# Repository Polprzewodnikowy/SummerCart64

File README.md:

# SummerCart64 - a fully open source N64 flashcart

**For non-technical description of the SummerCart64, please head to the https://summercart64.dev website!**

## Features

 - **ROM and Save Memory On-board**
   - 64 MiB SDRAM memory for game and save data (enough memory to support every retail game without compromise)
   - 16 MiB FLASH memory for bootloader and extended game data (with extended memory flashcart supports game ROMs up to 78 MiB)

 - **Game Saves**
   - EEPROM 4k/16k, SRAM and FlashRAM save types with an automatic writeback to the SD card (no reset button press required)

 - **Hardware-Dependent Game Features**
   - 64DD add-on emulation
   - Battery backed real time clock (RTC)

 - **Menu**
   - Dedicated open source menu written specifically for this flashcart - [N64FlashcartMenu](https://github.com/Polprzewodnikowy/N64FlashcartMenu)

 - **Game Development**
   - ~23.8 MiB/s peak transfer rate SD card interface
   - ~23.8 MiB/s peak transfer rate USB interface for data upload/download and debug functionality
   - PC app to access the flashcart features:
     - Game/save data upload/download
     - Feature enable control
     - Debug terminal
     - Access to the SD card
     - Firmware update
   - [UNFLoader](https://github.com/buu342/N64-UNFLoader) support
   - IS-Viewer 64 debug interface (fixed 64 kiB buffer with a movable base address)
   - 8 kiB on-chip buffer for general use
   - Status LED and button for general use
   - [UltraCIC_C](https://github.com/jago85/UltraCIC_C) emulation with automatic region switching and programmable seed/checksum values
   - N64 bootloader with support for IPL3 registers spoofing and loading menu from SD card

 - **Cartridge Production**
   - Initial programming via UART header or via dedicated JTAG/SWD interfaces
   - 3D printable shell

---

## Documentation

- [Quick startup guide](./docs/00_quick_startup_guide.md)
- [Memory map](./docs/01_memory_map.md)
- [N64 commands](./docs/02_n64_commands.md)
- [USB interface](./docs/03_usb_interface.md)
- [Config options](./docs/04_config_options.md)
- [FW and SW info](./docs/05_fw_and_sw_info.md)
- [Build guide](./docs/06_build_guide.md)

---

## How do I get one?

Most up to date information about purchasing/manufacturing options is available on https://summercart64.dev website!

If you want to order it yourself then I've prepared all necessary manufacturing files on the [PCBWay Shared Project](https://www.pcbway.com/project/member/shareproject/?bmbno=1046ED64-8AEE-44) site.

**Be careful**: this is an advanced project and it is assumed that you have enough knowledge about electronics.
Selecting wrong options or giving PCB manufacturer wrong information might result in an undesired time and/or money loss.
Boards also come unprogrammed from the manufacturer - you need to do **initial programming step** yourself after receiving the board.
**Price of the components is not included in the initial quote at the checkout** - manufacturer will contact you later with updated price.
To avoid problems _**please**_ read **both** [build guide](./docs/06_build_guide.md) and description on the shared project page **in full**.
If you have even slightest doubt about the ordering or programming process, it is better to leave it to someone experienced - ask in the [N64brew Discord server](https://discord.gg/8VNMKhxqQn) if that's the case.

**Full disclosure**: for every order made through [this link](https://www.pcbway.com/project/member/shareproject/?bmbno=1046ED64-8AEE-44) I will receive 10% of PCB manufacturing and PCB assembly service cost (price of the components is not included in the split). This is a great way of supporting further project development.

If you don't need a physical product but still want to support me then check the sponsor links on the [official website](https://summercart64.dev).

---

## High-level flashcart block diagram

---

## Finished example

---

## Acknowledgement

This project wouldn't be possible without these contributions:

- [64drive](https://64drive.retroactive.be) ([archived](https://web.archive.org/web/20240406215731/https://64drive.retroactive.be/)) orders being on permanent hold long before creating this repository.
- [EverDrive-64 X7](https://krikzz.com/our-products/cartridges/ed64x7.html) being disappointment for homebrew development (slow USB upload, unjustified price and overcomplicated SD card access).
  - Context: Both aforementioned products were priced at $199 in 2020. 64drive features made it a vastly more useful tool for homebrew development.
    Since then, 64drive had never been restocked and EverDrive-64 X7 price was lowered to $159 (as of May 2024).
- [Jan Goldacker (@jago85)](https://github.com/jago85) and his projects:
  - [Brutzelkarte](https://github.com/jago85/Brutzelkarte_FPGA) providing solid base for starting this project and sparking hope for true open source N64 flashcarts.
  - [UltraCIC_C](https://github.com/jago85/UltraCIC_C) reimplementation for easy integration in modern microcontrollers. Thanks also goes to everyone involved in N64 CIC reverse engineering.
- [N64brew](https://discord.gg/WqFgNWf) Discord server community being very helpful during flashcart development.
- [FatFs](http://elm-chan.org/fsw/ff/00index_e.html) FAT32/exFAT library being easiest to integrate in embedded environment.
- [Yakumono's (@LuigiBlood)](https://twitter.com/LuigiBlood) extensive [64DD documentation](https://github.com/LuigiBlood/64dd/wiki) and its implementation in various emulators.
- [Libdragon](https://github.com/DragonMinded/libdragon) open source N64 SDK project and its developers.
- [SERV](https://github.com/olofk/serv) bit-serial 32-bit RISC-V CPU soft core.

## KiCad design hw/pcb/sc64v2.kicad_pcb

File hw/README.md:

# SummerCart64 Hardware

Schematics and PCB design for SummerCart64 done in Autodesk Eagle software.

## TODO

- Expand documentation

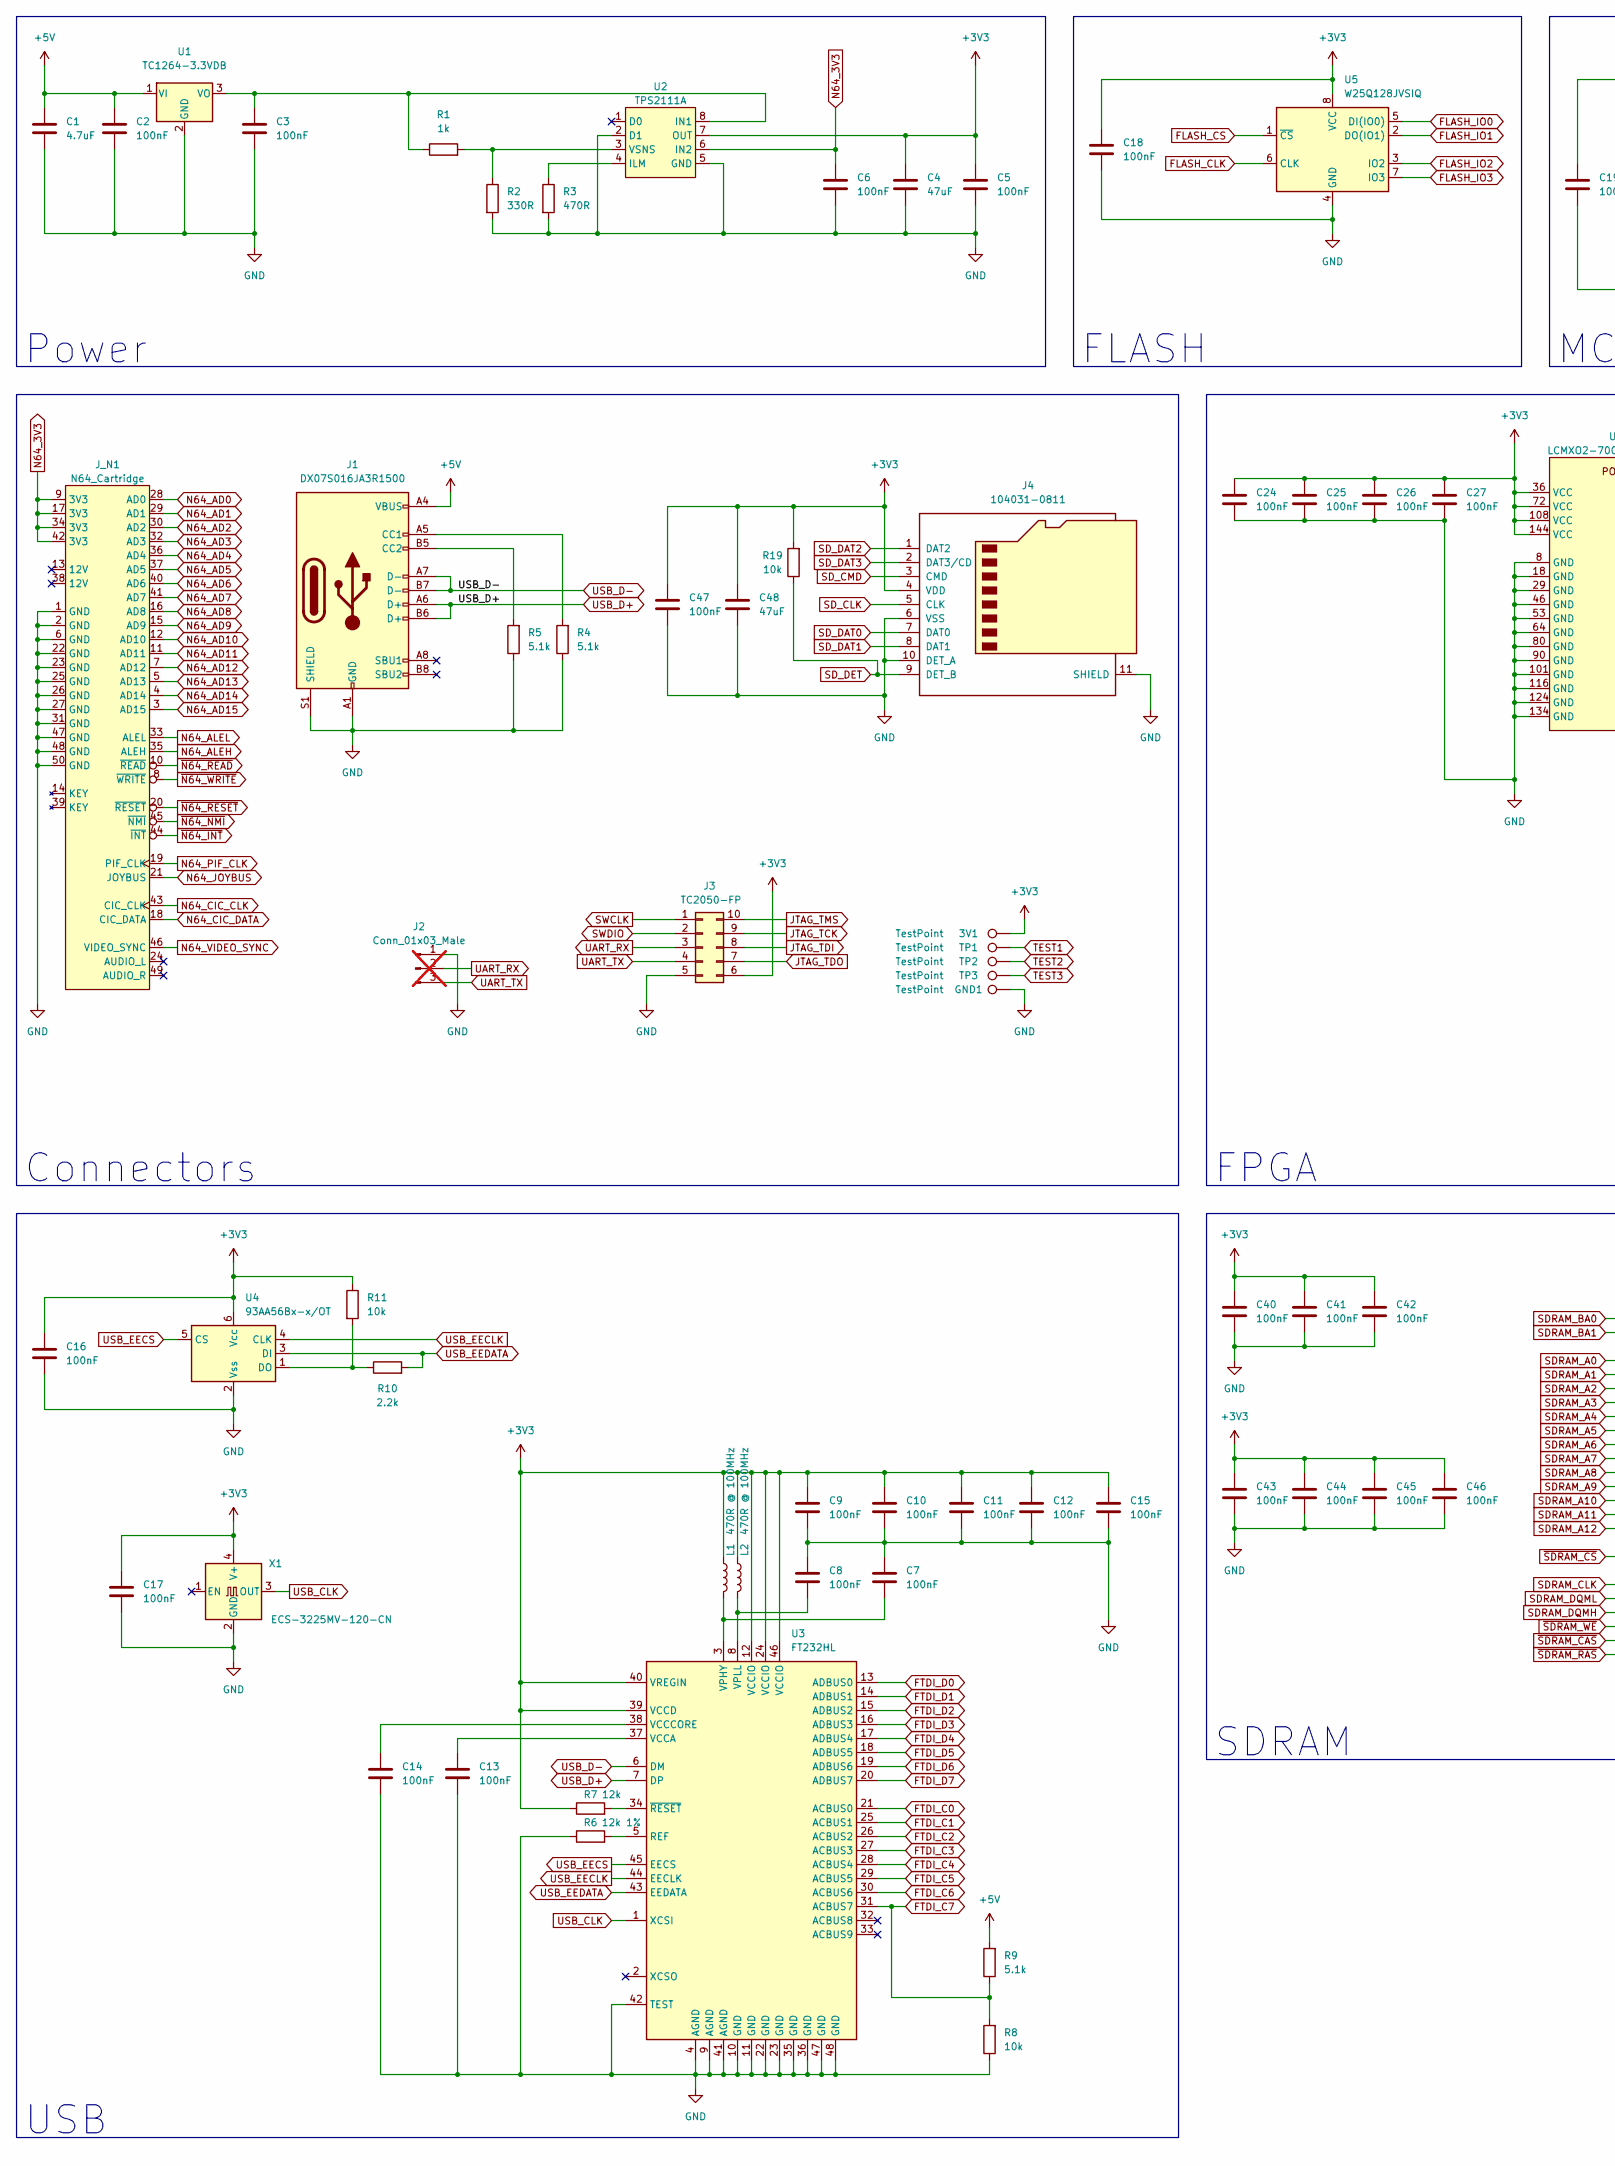
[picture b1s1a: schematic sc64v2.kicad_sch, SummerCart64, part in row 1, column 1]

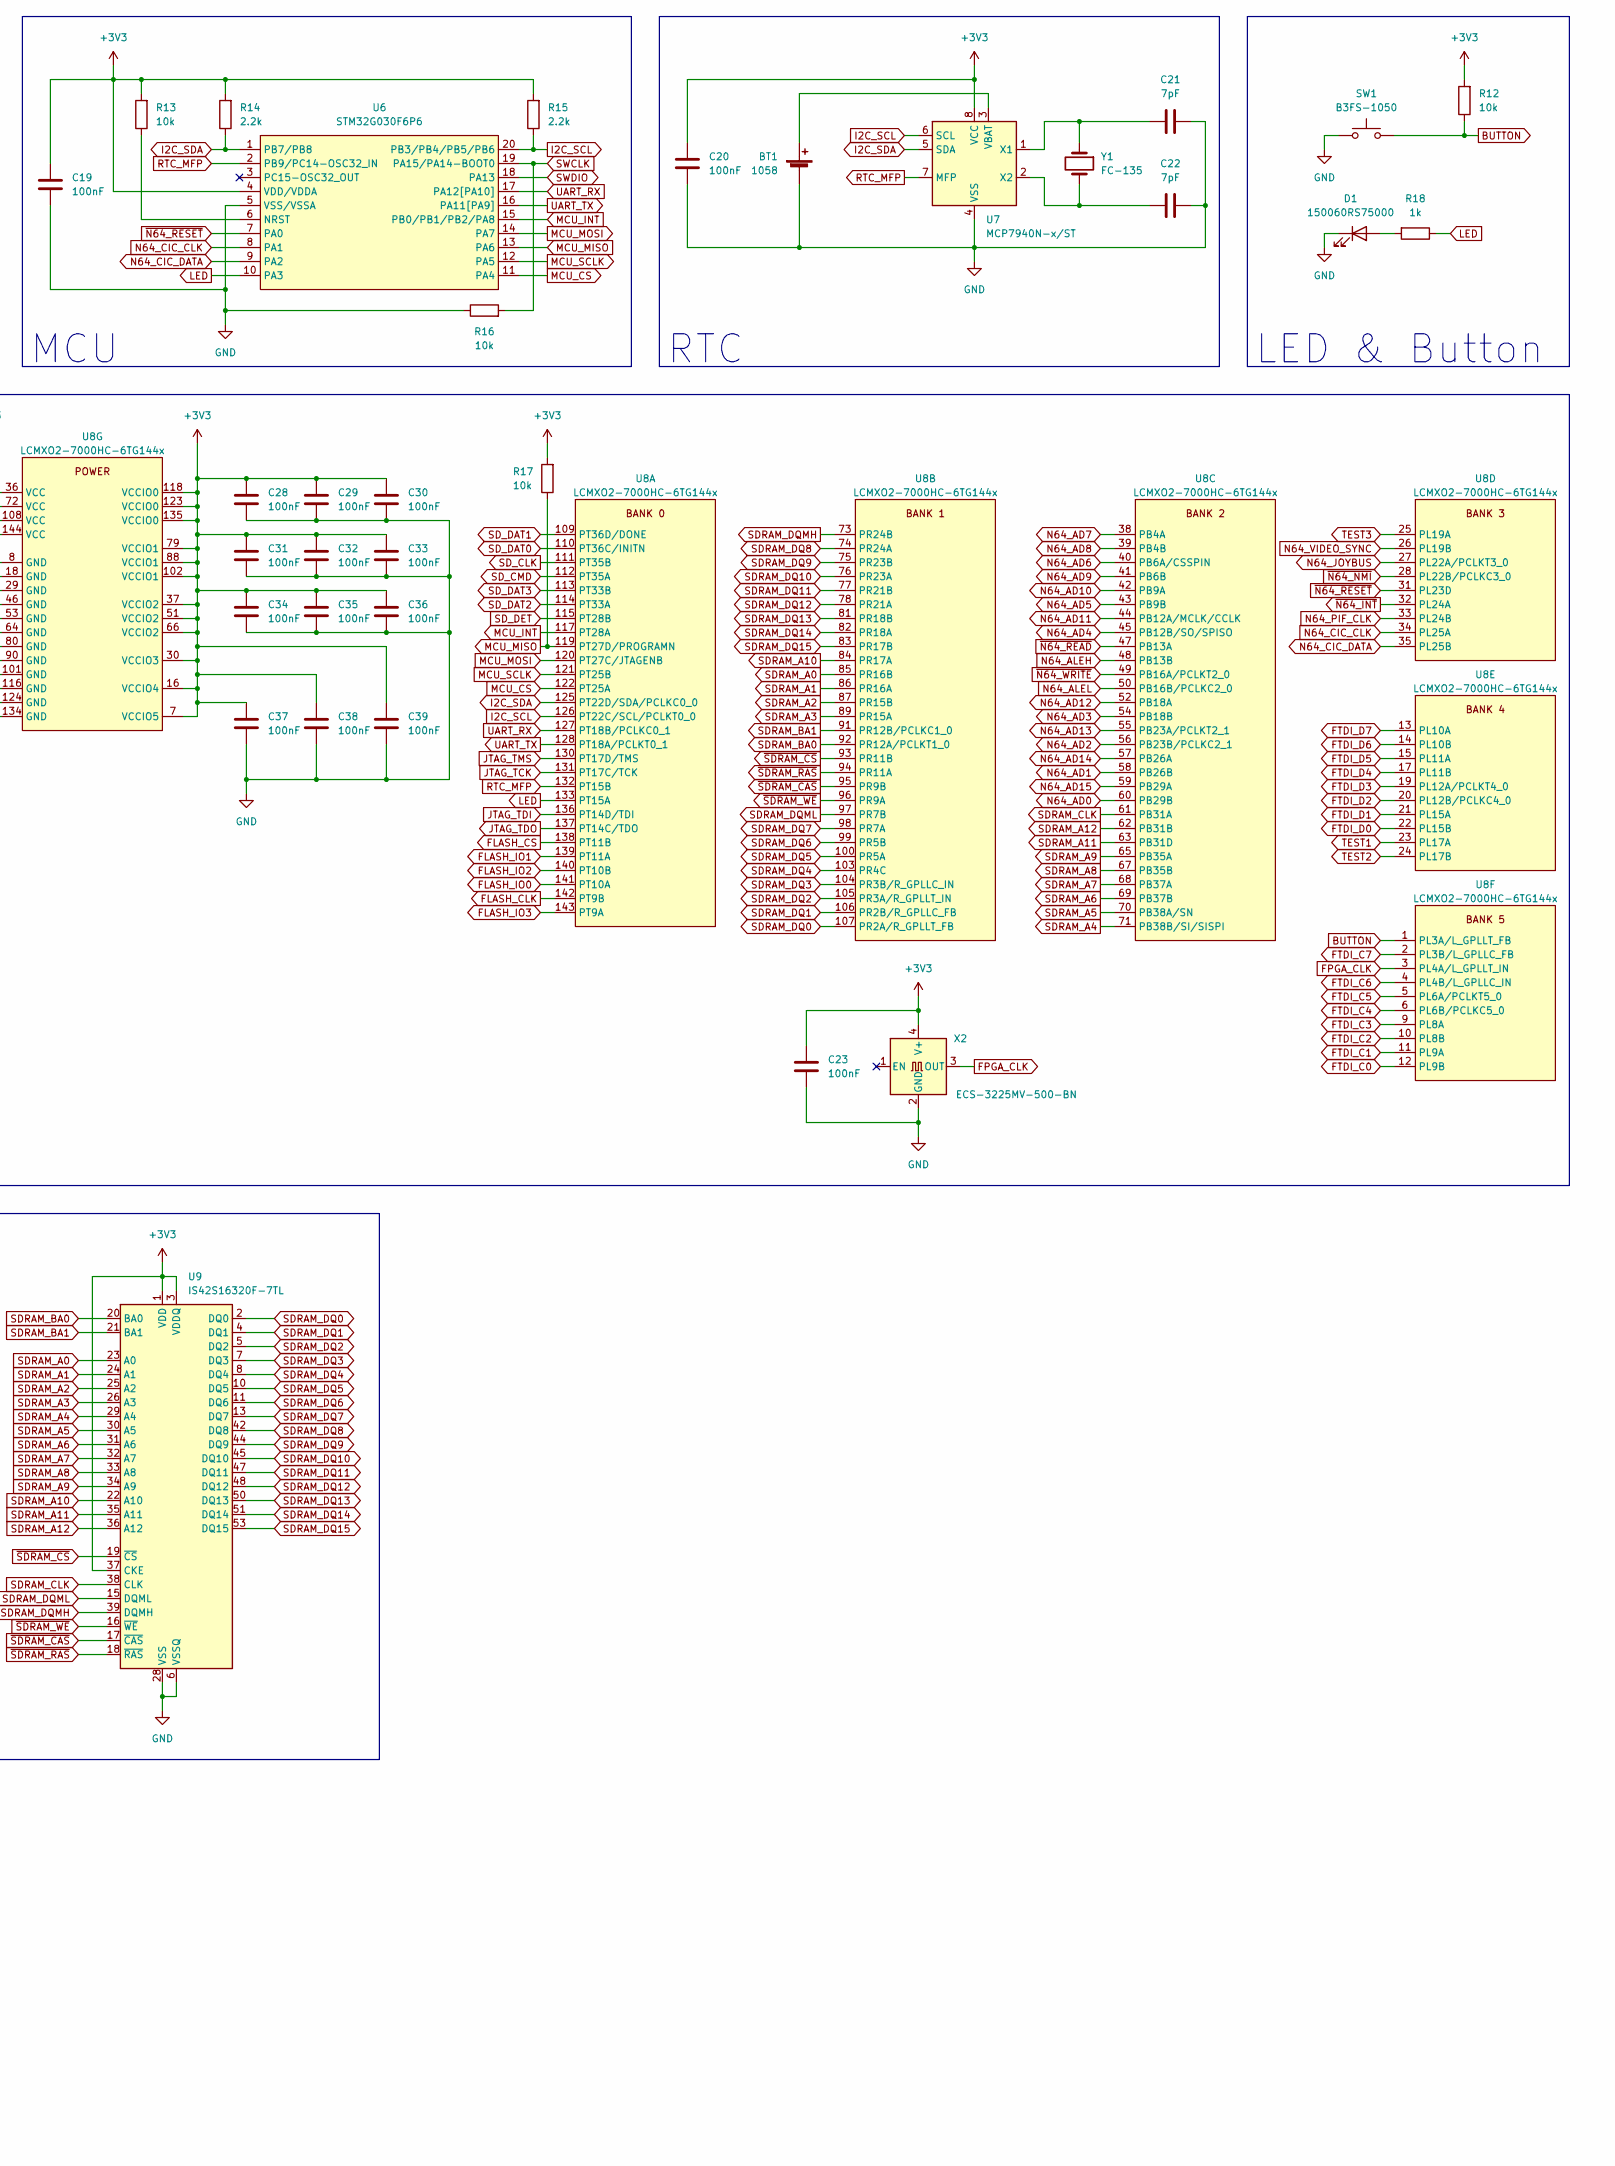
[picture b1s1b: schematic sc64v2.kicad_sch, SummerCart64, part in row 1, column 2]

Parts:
3V1: TestPoint; TestPoint_Pad_D1.5mm
BT1: 1058; BatteryHolder_Keystone_1058_1x2032
C1: 4.7uF; C_0603_1608Metric
C2, C3, C5, C6, C7, C8, C9, C10, C11, C12, C13, C14, C15, C16, C17, C18, C19, C20, C23, C24, C25, C26, C27, C28, C29, C30, C31, C32, C33, C34, C35, C36, C37, C38, C39, C40, C41, C42, C43, C44, C45, C46, C47: 100nF; C_0603_1608Metric
C4, C48: 47uF; C_0805_2012Metric
C21, C22: 7pF; C_0603_1608Metric
D1: 150060RS75000; LED_0603_1608Metric
GND1: TestPoint; TestPoint_Pad_D1.5mm
J1: DX07S016JA3R1500; USB_C_Receptacle_JAE_DX07S016JA1R1500
J2: Conn_01x03_Male; PinHeader_1x03_P2.54mm_Vertical; not fitted
J3: TC2050-FP; Tag-Connect_TC2050-IDC-FP_2x05_P1.27mm_Vertical
J4: 104031-0811; microSD_HC_Molex_104031-0811
J_N1: N64_Cartridge; N64_Edge
L1, L2: 470R @ 100MHz; L_0603_1608Metric
R1, R18: 1k; R_0603_1608Metric
R2: 330R; R_0603_1608Metric
R3: 470R; R_0603_1608Metric
R4, R5, R9: 5.1k; R_0603_1608Metric
R6: 12k 1%; R_0603_1608Metric
R7: 12k; R_0603_1608Metric
R8, R11, R12, R13, R16, R17, R19: 10k; R_0603_1608Metric
R10, R14, R15: 2.2k; R_0603_1608Metric
SW1: B3FS-1050; SW_SPST_Omron_B3FS-105xP
TP1, TP2, TP3: TestPoint; TestPoint_Pad_D1.5mm
U1: TC1264-3.3VDB; SOT-223-3_TabPin2
U2: TPS2111A; TSSOP-8_4.4x3mm_P0.65mm
U3: FT232HL; LQFP-48_7x7mm_P0.5mm
U4: 93AA56Bx-x/OT; SOT-23-6
U5: W25Q128JVSIQ; SOIC-8_5.23x5.23mm_P1.27mm
U6: STM32G030F6P6; TSSOP-20_4.4x6.5mm_P0.65mm
U7: MCP7940N-x/ST; TSSOP-8_4.4x3mm_P0.65mm
U8: LCMXO2-7000HC-6TG144x; TQFP-144_20x20mm_P0.5mm
U9: IS42S16320F-7TL; TSOP-II-54_22.2x10.16mm_P0.8mm
X1: ECS-3225MV-120-CN; Oscillator_SMD_SeikoEpson_SG8002CE-4Pin_3.2x2.5mm
X2: ECS-3225MV-500-BN; Oscillator_SMD_SeikoEpson_SG8002CE-4Pin_3.2x2.5mm
Y1: FC-135; Crystal_SMD_3215-2Pin_3.2x1.5mm

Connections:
+3V3: 3V1.1, C4.1, C5.1, C9.1, C10.1, C11.1, C12.1, C15.1, C16.2, C17.1, C18.1, C19.1, C20.1, C23.1, C24.1, C25.1, C26.1, C27.1, C28.1, C29.1, C30.1, C31.1, C32.1, C33.1, C34.1, C35.1, C36.1, C37.1, C38.1, C39.1, C40.1, C41.1, C42.1, C43.1, C44.1, C45.1, C46.1, C47.1, C48.1, J3.6, J4.4 (VDD), L1.1, L2.1, R7.1, R11.1, R12.2, R13.2, R14.2, R15.2, R17.2, R19.2, U2.7 (OUT), U3.12 (VCCIO), U3.24 (VCCIO), U3.39 (VCCD), U3.40 (VREGIN), U3.46 (VCCIO), U4.6 (Vсс), U5.8 (VCC), U6.4 (VDD/VDDA), U7.8 (VCC), U8.7 (VCCIO5), U8.16 (VCCIO4), U8.30 (VCCIO3), U8.36 (VCC), U8.37 (VCCIO2), U8.51 (VCCIO2), U8.66 (VCCIO2), U8.72 (VCC), U8.79 (VCCIO1), U8.88 (VCCIO1), U8.102 (VCCIO1), U8.108 (VCC), U8.118 (VCCIO0), U8.123 (VCCIO0), U8.135 (VCCIO0), U8.144 (VCC), U9.1 (VDD), U9.3 (VDDQ), U9.9 (VDDQ), U9.14 (VDD), U9.27 (VDD), U9.37 (CKE), U9.43 (VDDQ), U9.49 (VDDQ), X1.4 (V+), X2.4 (V+)
+5V: C1.1, C2.1, J1.A4 (VBUS), J1.A9 (VBUS), J1.B4 (VBUS), J1.B9 (VBUS), R9.2, U1.1 (VI)
BUTTON: R12.1, SW1.2, U8.1 (PL3A/L_GPLLT_FB)
FLASH_CLK: U5.6 (CLK), U8.142 (PT9B)
FLASH_CS: U5.1 (~CS), U8.138 (PT11B)
FLASH_IO0: U5.5 (DI(IO0)), U8.141 (PT10A)
FLASH_IO1: U5.2 (DO(IO1)), U8.139 (PT11A)
FLASH_IO2: U5.3 (IO2), U8.140 (PT10B)
FLASH_IO3: U5.7 (IO3), U8.143 (PT9A)
FPGA_CLK: U8.3 (PL4A/L_GPLLT_IN), X2.3 (OUT)
FTDI_C0: U3.21 (ACBUS0), U8.12 (PL9B)
FTDI_C1: U3.25 (ACBUS1), U8.11 (PL9A)
FTDI_C2: U3.26 (ACBUS2), U8.10 (PL8B)
FTDI_C3: U3.27 (ACBUS3), U8.9 (PL8A)
FTDI_C4: U3.28 (ACBUS4), U8.6 (PL6B/PCLKC5_0)
FTDI_C5: U3.29 (ACBUS5), U8.5 (PL6A/PCLKT5_0)
FTDI_C6: U3.30 (ACBUS6), U8.4 (PL4B/L_GPLLC_IN)
FTDI_C7: R8.2, R9.1, U3.31 (ACBUS7), U8.2 (PL3B/L_GPLLC_FB)
FTDI_D0: U3.13 (ADBUS0), U8.22 (PL15B)
FTDI_D1: U3.14 (ADBUS1), U8.21 (PL15A)
FTDI_D2: U3.15 (ADBUS2), U8.20 (PL12B/PCLKC4_0)
FTDI_D3: U3.16 (ADBUS3), U8.19 (PL12A/PCLKT4_0)
FTDI_D4: U3.17 (ADBUS4), U8.17 (PL11B)
FTDI_D5: U3.18 (ADBUS5), U8.15 (PL11A)
FTDI_D6: U3.19 (ADBUS6), U8.14 (PL10B)
FTDI_D7: U3.20 (ADBUS7), U8.13 (PL10A)
GND: BT1.2 (-), C1.2, C2.2, C3.2, C4.2, C5.2, C6.2, C7.1, C8.2, C9.2, C10.2, C11.2, C12.2, C13.1, C14.1, C15.2, C16.1, C17.2, C18.2, C19.2, C20.2, C21.2, C22.1, C23.2, C24.2, C25.2, C26.2, C27.2, C28.2, C29.2, C30.2, C31.2, C32.2, C33.2, C34.2, C35.2, C36.2, C37.2, C38.2, C39.2, C40.2, C41.2, C42.2, C43.2, C44.2, C45.2, C46.2, C47.2, C48.2, D1.1 (K), GND1.1, J1.A1 (GND), J1.A12 (GND), J1.B1 (GND), J1.B12 (GND), J1.S1 (SHIELD), J2.1, J3.5, J4.6 (VSS), J4.10 (DET_A), J4.11 (SHIELD), J_N1.1 (GND), J_N1.2 (GND), J_N1.6 (GND), J_N1.22 (GND), J_N1.23 (GND), J_N1.25 (GND), J_N1.26 (GND), J_N1.27 (GND), J_N1.31 (GND), J_N1.47 (GND), J_N1.48 (GND), J_N1.50 (GND), R2.2, R3.2, R4.1, R5.1, R6.1, R8.1, R16.1, SW1.1, U1.2 (GND), U2.2 (D1), U2.5 (GND), U3.4 (AGND), U3.9 (AGND), U3.10 (GND), U3.11 (GND), U3.22 (GND), U3.23 (GND), U3.35 (GND), U3.36 (GND), U3.41 (AGND), U3.42 (TEST), U3.47 (GND), U3.48 (GND), U4.2 (Vss), U5.4 (GND), U6.5 (VSS/VSSA), U7.4 (VSS), U8.8 (GND), U8.18 (GND), U8.29 (GND), U8.46 (GND), U8.53 (GND), U8.64 (GND), U8.80 (GND), U8.90 (GND), U8.101 (GND), U8.116 (GND), U8.124 (GND), U8.134 (GND), U9.6 (VSSQ), U9.12 (VSSQ), U9.28 (VSS), U9.41 (VSS), U9.46 (VSSQ), U9.52 (VSSQ), U9.54 (VSS), X1.2 (GND), X2.2 (GND)
I2C_SCL: R15.1, U6.20 (PB3/PB4/PB5/PB6), U7.6 (SCL), U8.126 (PT22C/SCL/PCLKT0_0)
I2C_SDA: R14.1, U6.1 (PB7/PB8), U7.5 (SDA), U8.125 (PT22D/SDA/PCLKC0_0)
JTAG_TCK: J3.9, U8.131 (PT17C/TCK)
JTAG_TDI: J3.8, U8.136 (PT14D/TDI)
JTAG_TDO: J3.7, U8.137 (PT14C/TDO)
JTAG_TMS: J3.10, U8.130 (PT17D/TMS)
LED: R18.1, U6.10 (PA3), U8.133 (PT15A)
MCU_CS: U6.11 (PA4), U8.122 (PT25A)
MCU_INT: U6.15 (PB0/PB1/PB2/PA8), U8.117 (PT28A)
MCU_MISO: R17.1, U6.13 (PA6), U8.119 (PT27D/PROGRAMN)
MCU_MOSI: U6.14 (PA7), U8.120 (PT27C/JTAGENB)
MCU_SCLK: U6.12 (PA5), U8.121 (PT25B)
N64_3V3: C6.1, J_N1.9 (3V3), J_N1.17 (3V3), J_N1.34 (3V3), J_N1.42 (3V3), U2.6 (IN2)
N64_AD0: J_N1.28 (AD0), U8.60 (PB29B)
N64_AD1: J_N1.29 (AD1), U8.58 (PB26B)
N64_AD2: J_N1.30 (AD2), U8.56 (PB23B/PCLKC2_1)
N64_AD3: J_N1.32 (AD3), U8.54 (PB18B)
N64_AD4: J_N1.36 (AD4), U8.45 (PB12B/SO/SPISO)
N64_AD5: J_N1.37 (AD5), U8.43 (PB9B)
N64_AD6: J_N1.40 (AD6), U8.40 (PB6A/CSSPIN)
N64_AD7: J_N1.41 (AD7), U8.38 (PB4A)
N64_AD8: J_N1.16 (AD8), U8.39 (PB4B)
N64_AD9: J_N1.15 (AD9), U8.41 (PB6B)
N64_AD10: J_N1.12 (AD10), U8.42 (PB9A)
N64_AD11: J_N1.11 (AD11), U8.44 (PB12A/MCLK/CCLK)
N64_AD12: J_N1.7 (AD12), U8.52 (PB18A)
N64_AD13: J_N1.5 (AD13), U8.55 (PB23A/PCLKT2_1)
N64_AD14: J_N1.4 (AD14), U8.57 (PB26A)
N64_AD15: J_N1.3 (AD15), U8.59 (PB29A)
N64_ALEH: J_N1.35 (ALEH), U8.48 (PB13B)
N64_ALEL: J_N1.33 (ALEL), U8.50 (PB16B/PCLKC2_0)
N64_CIC_CLK: J_N1.43 (CIC_CLK), U6.8 (PA1), U8.34 (PL25A)
N64_CIC_DATA: J_N1.18 (CIC_DATA), U6.9 (PA2), U8.35 (PL25B)
N64_JOYBUS: J_N1.21 (JOYBUS), U8.27 (PL22A/PCLKT3_0)
N64_PIF_CLK: J_N1.19 (PIF_CLK), U8.33 (PL24B)
N64_VIDEO_SYNC: J_N1.46 (VIDEO_SYNC), U8.26 (PL19B)
unnamed: BT1.1 (+), U7.3 (VBAT)
unnamed: D1.2 (A), R18.2
unnamed: J1.A5 (CC1), R4.2
unnamed: J1.B5 (CC2), R5.2
unnamed: C3.1, R1.1, U1.3 (VO), U2.8 (IN1)
unnamed: R3.1, U2.4 (ILM)
unnamed: R1.2, R2.1, U2.3 (VSNS)
unnamed: R6.2, U3.5 (REF)
unnamed: C13.2, U3.37 (VCCA)
unnamed: C14.2, U3.38 (VCCCORE)
unnamed: C7.2, L1.2, U3.3 (VPHY)
unnamed: C8.1, L2.2, U3.8 (VPLL)
unnamed: R7.2, U3.34 (~RESET)
unnamed: R10.1, R11.2, U4.1 (DO)
unnamed: R13.1, U6.6 (NRST)
unnamed: C21.1, U7.1 (X1), Y1.1
unnamed: C22.2, U7.2 (X2), Y1.2
RTC_MFP: U6.2 (PB9/PC14-OSC32_IN), U7.7 (MFP), U8.132 (PT15B)
SDRAM_A0: U8.85 (PR16B), U9.23 (A0)
SDRAM_A1: U8.86 (PR16A), U9.24 (A1)
SDRAM_A2: U8.87 (PR15B), U9.25 (A2)
SDRAM_A3: U8.89 (PR15A), U9.26 (A3)
SDRAM_A4: U8.71 (PB38B/SI/SISPI), U9.29 (A4)
SDRAM_A5: U8.70 (PB38A/SN), U9.30 (A5)
SDRAM_A6: U8.69 (PB37B), U9.31 (A6)
SDRAM_A7: U8.68 (PB37A), U9.32 (A7)
SDRAM_A8: U8.67 (PB35B), U9.33 (A8)
SDRAM_A9: U8.65 (PB35A), U9.34 (A9)
SDRAM_A10: U8.84 (PR17A), U9.22 (A10)
SDRAM_A11: U8.63 (PB31D), U9.35 (A11)
SDRAM_A12: U8.62 (PB31B), U9.36 (A12)
SDRAM_BA0: U8.92 (PR12A/PCLKT1_0), U9.20 (BA0)
SDRAM_BA1: U8.91 (PR12B/PCLKC1_0), U9.21 (BA1)
SDRAM_CLK: U8.61 (PB31A), U9.38 (CLK)
SDRAM_DQ0: U8.107 (PR2A/R_GPLLT_FB), U9.2 (DQ0)
SDRAM_DQ1: U8.106 (PR2B/R_GPLLC_FB), U9.4 (DQ1)
SDRAM_DQ2: U8.105 (PR3A/R_GPLLT_IN), U9.5 (DQ2)
SDRAM_DQ3: U8.104 (PR3B/R_GPLLC_IN), U9.7 (DQ3)
SDRAM_DQ4: U8.103 (PR4C), U9.8 (DQ4)
SDRAM_DQ5: U8.100 (PR5A), U9.10 (DQ5)
SDRAM_DQ6: U8.99 (PR5B), U9.11 (DQ6)
SDRAM_DQ7: U8.98 (PR7A), U9.13 (DQ7)
SDRAM_DQ8: U8.74 (PR24A), U9.42 (DQ8)
SDRAM_DQ9: U8.75 (PR23B), U9.44 (DQ9)
SDRAM_DQ10: U8.76 (PR23A), U9.45 (DQ10)
SDRAM_DQ11: U8.77 (PR21B), U9.47 (DQ11)
SDRAM_DQ12: U8.78 (PR21A), U9.48 (DQ12)
SDRAM_DQ13: U8.81 (PR18B), U9.50 (DQ13)
SDRAM_DQ14: U8.82 (PR18A), U9.51 (DQ14)
SDRAM_DQ15: U8.83 (PR17B), U9.53 (DQ15)
SDRAM_DQMH: U8.73 (PR24B), U9.39 (DQMH)
SDRAM_DQML: U8.97 (PR7B), U9.15 (DQML)
SD_CLK: J4.5 (CLK), U8.111 (PT35B)
SD_CMD: J4.3 (CMD), U8.112 (PT35A)
SD_DAT0: J4.7 (DAT0), U8.110 (PT36C/INITN)
SD_DAT1: J4.8 (DAT1), U8.109 (PT36D/DONE)
SD_DAT2: J4.1 (DAT2), U8.114 (PT33A)
SD_DAT3: J4.2 (DAT3/CD), U8.113 (PT33B)
SD_DET: J4.9 (DET_B), R19.1, U8.115 (PT28B)
SWCLK: J3.1, R16.2, U6.19 (PA15/PA14-BOOT0)
SWDIO: J3.2, U6.18 (PA13)
TEST1: TP1.1, U8.23 (PL17A)
TEST2: TP2.1, U8.24 (PL17B)
TEST3: TP3.1, U8.25 (PL19A)
UART_RX: J2.2, J3.3, U6.17 (PA12[PA10]), U8.127 (PT18B/PCLKC0_1)
UART_TX: J2.3, J3.4, U6.16 (PA11[PA9]), U8.128 (PT18A/PCLKT0_1)
USB_CLK: U3.1 (XCSI), X1.3 (OUT)
USB_D+: J1.A6 (D+), J1.B6 (D+), U3.7 (DP)
USB_D-: J1.A7 (D-), J1.B7 (D-), U3.6 (DM)
USB_EECLK: U3.44 (EECLK), U4.4 (CLK)
USB_EECS: U3.45 (EECS), U4.5 (CS)
USB_EEDATA: R10.2, U3.43 (EEDATA), U4.3 (DI)
~N64_INT: J_N1.44 (~INT), U8.32 (PL24A)
~N64_NMI: J_N1.45 (~NMI), U8.28 (PL22B/PCLKC3_0)
~N64_READ: J_N1.10 (~READ), U8.47 (PB13A)
~N64_RESET: J_N1.20 (~RESET), U6.7 (PA0), U8.31 (PL23D)
~N64_WRITE: J_N1.8 (~WRITE), U8.49 (PB16A/PCLKT2_0)
~SDRAM_CAS: U8.95 (PR9B), U9.17 (~CAS)
~SDRAM_CS: U8.93 (PR11B), U9.19 (~CS)
~SDRAM_RAS: U8.94 (PR11A), U9.18 (~RAS)
~SDRAM_WE: U8.96 (PR9A), U9.16 (~WE)

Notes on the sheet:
Power
USB
LED & Button
RTC
Connectors
MCU
FPGA
FLASH
SDRAM

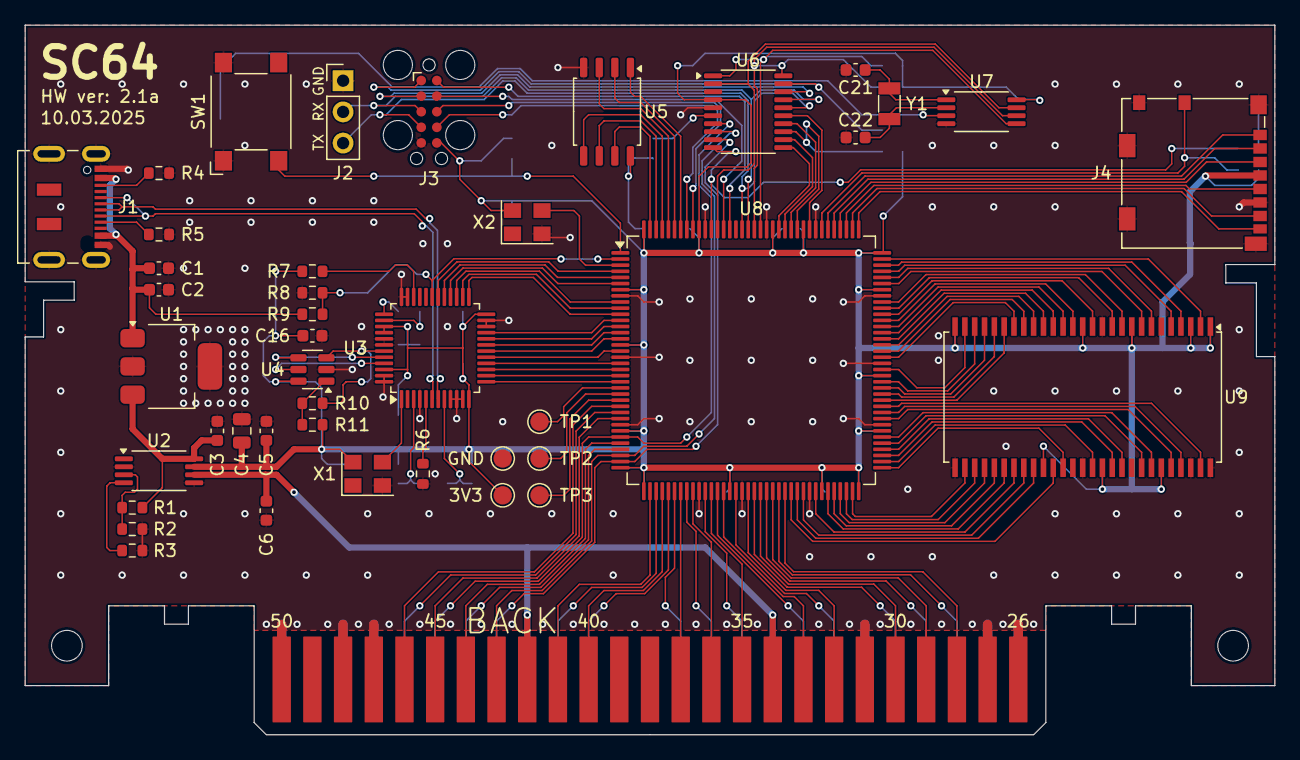
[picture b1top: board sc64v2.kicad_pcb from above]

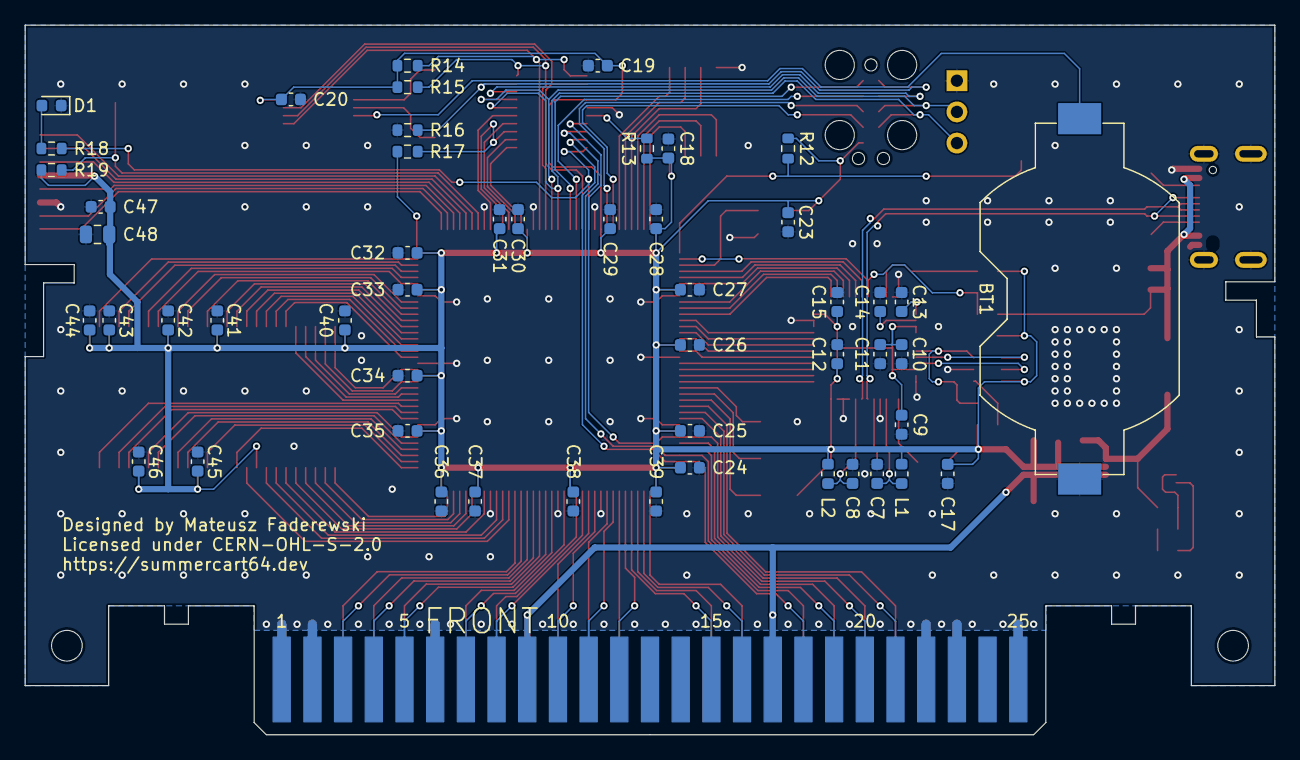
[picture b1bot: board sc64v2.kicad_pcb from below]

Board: 2 copper layers, 101.8 x 57.8 mm, 94 parts (51 on the bottom side), 144 nets.

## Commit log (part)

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2026-03-28 Fix SC64 SD read: use physical address for DMA + cache invalidate
    SC64 firmware does DMA directly to RDRAM using physical addresses.
    Our code passed KSEG0 virtual address (0x80xxxxxx) but SC64 needs
    physical (0x00xxxxxx). Fixed: strip upper 3 bits with & 0x1FFFFFFF.
    Also: invalidate data cache after DMA so CPU sees the new data
    (SC64 writes to RDRAM bypassing CPU cache).
    https://claude.ai/code/session_01RAifKp5aeprBiRruyxTAdk
2026-03-28 Portal BFS room traversal + per-vertex Gouraud shading — CAVES RENDERING ON N64
    First ever Tomb Raider 1 level geometry rendered on Nintendo 64.
    Real .PHD level data from the original 1996 game, parsed and drawn
    on real N64 hardware via SC64 flashcart.
    - BFS portal traversal renders all connected rooms (up to 60)
    - Per-vertex Gouraud shading from original TR1 light values
    - Free-fly camera with analog stick
2026-03-28 Pre-convert all textures to 16x16 RGBA16 at load time
    - Eliminates ALL per-frame texture conversion and buffer reuse issues
    - Each object texture gets its own permanent RGBA16 surface in heap
    - No CI8/TLUT complexity — pure RGBA16 with bilinear filtering
    - Render loop just calls rdpq_tex_upload with pre-made surface
    - ~1MB for ~2000 textures (16x16x2 bytes each)
    - UV coords pre-computed at load time per texture
2026-03-28 Add Lara model rendering with bone tree traversal
    Renders Lara's 3D mesh at her spawn position using the full bone
    hierarchy (push/pop matrix stack). Decodes first animation frame
    for the T-pose rotations. Each of her ~15 body part meshes is
    transformed through the bone tree and drawn with the same textured
    triangle pipeline as rooms. Lara is drawn fully lit (shade=1.0)
    after rooms for proper depth ordering.
2026-03-28 Fix room loading: track camera room in both fly and walk modes
    Room detection was inside the walk_mode block, so in fly mode
    lara_room never updated and BFS always showed the same rooms.
    Now room tracking always runs — new rooms load as you explore.
    https://claude.ai/code/session_01RAifKp5aeprBiRruyxTAdk
2026-03-28 D-pad up/down = fly up/down, C-buttons = move/strafe
    D-pad: up/down fly vertically, left/right strafe
    C-buttons: up/down move forward/back, left/right strafe
    https://claude.ai/code/session_01RAifKp5aeprBiRruyxTAdk
2026-03-28 Anti-aliasing: VI edge filter + RDP per-triangle AA
    - VI: FILTERS_RESAMPLE_ANTIALIAS (divot filter for edge smoothing)
    - RDP: AA_STANDARD for per-pixel coverage-based anti-aliasing
    - Both applied to all geometry (rooms, Lara, items, static objects)
    - Should smooth jagged edges on Lara's legs and all triangle edges
    https://claude.ai/code/session_01RAifKp5aeprBiRruyxTAdk
2026-03-29 Wire up actual sound playback through libdragon mixer
    - Created pcm_wave_t wrapper for in-memory PCM → waveform_t
    - Cycles through parsed TR1 samples, plays one every ~7 seconds
    - Uses mixer channel 0 at 50% volume
    - Cache flush before playback for DMA coherency
    - Should hear actual TR1 cave ambient sound effects!
    https://claude.ai/code/session_01RAifKp5aeprBiRruyxTAdk
2026-03-29 Wall collision: 512-unit probe ahead + audio debug on pause
    - Wall collision now probes 512 units ahead of destination to catch
    thin wall sectors that fast movement could skip over
    - Wall slide tries X-only then Z-only when blocked
    - Pause screen now shows full sound data debug: sample_data pointer,
    sizes, index count, flags, compressed/full sizes
    - This helps diagnose why audio shows 0 samples
2026-03-29 Debug: disable textures/fog to test GL geometry only
    Temporarily disabled GL textures and fog to isolate whether the
    garbled rendering is a geometry/projection issue or a texture issue.
    Should show flat-shaded cave with vertex colors only.
    https://claude.ai/code/session_01RAifKp5aeprBiRruyxTAdk
2026-03-29 Interleaved verts, more rooms, clamp textures, re-enable pause
    Performance + quality:
    - Interleaved vertex struct (24 bytes: 3f pos + 4ub color + 2f tc)
    Single cache flush instead of 3 separate arrays
    - GLubyte colors instead of GLfloat (4 bytes vs 16 bytes/vertex)
    - Per-face distance cull (12K unit radius) to skip far geometry
    - 16 rooms via portal BFS (was 5) to reduce pop-in
2026-03-29 Fix sparse textures: disable face decimation and revert fog
    Face decimation (f += face_skip) caused visible black holes because:
    1. Faces are sorted by texture — skipping every Nth face breaks
    texture batching and leaves gaps in spatial coverage
    2. Dark fog color (R=0.08) made distant faces appear nearly black
    Fixes:
    - Disable face_skip in render loop (always f++ for all faces)
2026-03-29 Phase 3: Textured RDPQ far pass with TMEM uploads
    Far pass now renders textured + shaded triangles via rdpq:
    - TRIFMT_SHADE_TEX format: {X, Y, R, G, B, A, S, T, INV_W}
    - rdpq_tex_upload(TILE0, &tex_surfs[idx], NULL) for each texture
    - Texture batching: only uploads when texture index changes
    (faces are pre-sorted by texture from load time)
    - Tex coords in pixel space (matching rdpq convention)
2026-03-29 Fix black gaps + OOM: disable face decimation, use rspq_wait
    1. Black gaps in far pass: face decimation (skip every Nth face)
    caused visible holes because faces are texture-sorted, not
    spatially sorted. Disabled — all far faces now draw.
    2. OOM: switched from rspq_flush (non-blocking send) to rspq_wait
    (blocking drain) at three points:
    - Before every texture upload
2026-03-29 On-demand mip generation for far pass
    Instead of pre-allocating mip surfaces for all 880 textures (OOM'd
    at 560KB uncached), generate mips on-the-fly for just the ~8
    textures uploaded per frame.
    Implementation:
    - One reusable 16×16 RGBA16 buffer = 512 bytes uncached
    - Box-filter 32→16 (2×2 average) computed on each far upload
2026-03-29 Lambert-style mip system: two LOD levels + fallback chain
    Following James Lambert's N64 optimization techniques:
    Mip levels:
    - Level 0: 32×32 base (near/overlap, full TMEM: 2048 bytes)
    - Level 1: 16×16 on-demand (mid distance, 512 bytes TMEM)
    - Level 2: 8×8 on-demand (very far, 128 bytes TMEM)
    Two reusable uncached buffers: 512 + 128 = 640 bytes total.
2026-03-29 Fix cave void + static mesh flicker
    1. Portal near-plane crossing: when a portal has some vertices
    behind the camera and some in front, the projected screen rect
    only covered the in-front vertices (too small). The portal
    actually spans the entire parent clip region when it crosses
    the near plane. Fix: expand to parent clip rect when any
    portal vertex is behind camera.
2026-03-29 Factor portal connectivity into per-room draw distance
    Rooms with more portal connections (junction areas) get a draw
    distance boost of ~1 sector per portal. This keeps important
    connecting rooms visible longer while small dead-end rooms still
    cull early.
    https://claude.ai/code/session_01CRpPKHXrP3YxsjPEStD62Z
2026-03-29 Performance: texture sort + back-cull + bind budget
    Three optimizations targeting the 73 texture binds / 7 FPS bottleneck:
    1. Sort faces by texture at load time (insertion sort per room).
    Groups same-texture faces together so consecutive faces share
    the same bind. Converts ~73 binds → ~15-20 unique textures.
    2. Per-face back-cull in GL near pass. Check first vertex depth
    (camera-space Z) before any vertex processing. Faces behind
2026-03-29 Fix Lara head, screen edge culling, save 704KB heap via zero-copy tex_pages
    Lara head invisible:
    - Changed z-reject (rz < 32 → vis=false; break) to z-clamp
    (rz < 4 → rz = 4). The old reject dropped entire faces if ANY
    vertex was close to camera. Head mesh vertices in 3rd-person view
    could be within 32 units, causing the whole head to vanish.
    - Exempt Lara from NEAR_FACE_BUDGET — she's fixed cost (~6ms) and
2026-03-29 Add portal64-still-alive to research log
    Key borrowable techniques:
    - Doorway frustum narrowing (construct per-portal frustum, recurse
    with tighter bounds — directly maps to TR1 room portals)
    - 4-bit twoTone textures (4bpp grayscale + combiner colorize =
    512B/tile vs 1KB CI8 — halves TMEM usage)
    - Pre-computed room non-visibility bitmask
2026-03-30 Fix uninitialized variable warnings for effective budgets
    Initialize eff_near_face_budget, eff_near_tri_budget, eff_far_tri_budget
    at declaration. They get recomputed each frame but the pause screen
    could reference them before the first frame completes.
    https://claude.ai/code/session_01CRpPKHXrP3YxsjPEStD62Z
2026-03-30 Fix tier system: distance-based classification, never skip tiers
    Previously rooms were classified by ring (ring-1=near, ring-2=far),
    causing rooms to jump from Near directly to XFar, skipping MidFar
    and Far tiers entirely. A connected room at 10000 units rendered
    the same as one at 500 units (both Near/green).
    Now: ALL rooms (except current room) classified purely by distance
    against g_dist_mid threshold:
2026-03-30 Add per-ring room count diagnostics to debug void between tiers
    Page 0 now shows: Rings:N/N/N/N/N (rooms found per ring depth).
    - Ring[0] = current + ring1 total
    - Ring[1] = new rooms found at depth 2
    - Ring[2] = depth 3
    - Ring[3] = depth 4
    - Ring[4] = depth 5
2026-03-30 Flip baked pass sort: front-to-back (closest first)
    Was back-to-front (farthest first, painter's algorithm). This meant
    the farthest room consumed the entire tri budget, and close baked
    rooms never rendered — creating the void.
    Now front-to-back: closest baked rooms render first, getting full
    budget priority. Z-fighting is possible without zbuf but acceptable
    for testing whether close baked rooms actually render.
2026-03-30 Set default budgets: tex_face=350, tex_tri=550, bkd_tri=450, draw=33000
    Per user tuning on hardware.
    https://claude.ai/code/session_01CRpPKHXrP3YxsjPEStD62Z
2026-03-30 AegisTex ROM streaming + CI4 for all tiers including Near
    Build tool:
    - build_full_rom.py now embeds .atx file in ROM with ATX_ROM_OFFSET
    - Usage: build_full_rom.py rom assets output [baked] [ci8] [atx]
    Runtime — ROM-backed CI4 loading:
    - Reads ATX1 header from ROM, gets per-tile format records
    - DMA CI4 payloads (palette + packed nibbles) from ROM
2026-03-30 Fix T3D Lara compile + rendering: vert limit, winding, camera pitch
    - Fix vertex buffer overflow: T3D max is 70, was allowing 80
    - Fix triangle winding: TR1 CW → T3D CCW (swap v1/v2)
    - Fix camera pitch: scale XZ by cos(pitch) in look_at target
    - Fix linker: --allow-multiple-definition for asset_load collision
    - Record rdpq mode + T3D draw flags inside rspq_blocks
    - Suppress unused-but-set warnings with (void) casts
2026-03-30 Complete Tier 1: tests, command ref, decoder tool, validation workflow
    Fixes from real T3D source (verified against t3d.c rspq_write calls):
    - TRI_DRAW is 2 words (was 1): W0=v0_dmem, W1=v1|v2 packed
    - DRAWFLAGS is 2 words (was 1): W0=cull_mask, W1=rdp_cmd
    - PROJ_SET is 1 word (was 2): addr in 24-bit args field
    COMMAND_REFERENCE.md: Full table with source file, line number, payload
    format, render semantic, and TR1 usage priority (P0-P3) for each of
2026-03-30 Strict VERT_LOAD validation: reject implausible input_size and address
    VERT_LOAD now requires:
    - input_size <= 1120 bytes (70 verts max = 35 packed pairs * 32)
    - input_size must be a multiple of 32 (T3DVertPacked alignment)
    - RDRAM address must be >= 0x1000 (not in MMIO space)
    - RDRAM address must be within RDRAM bounds
    Implausible VERT_LOAD commands (from misaligned scans) now
2026-03-31 Path B: CPU-side rspq intercept via SP_STATUS SIG_MORE hook
    cpu_intercept.h/c: Captures rspq commands at the CPU publish boundary.
    Hook: SP_STATUS write with SIG_MORE (signal 7) set.
    When CPU sets this, it has just written new commands to the rspq
    RDRAM buffer and is telling the RSP to process them.
    Strategy:
    1. Detect rspq buffer RDRAM addresses from DMA patterns

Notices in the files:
hw/pcb/sc64v2.kicad_pcb:
Licensed under CERN-OHL-S-2.0
